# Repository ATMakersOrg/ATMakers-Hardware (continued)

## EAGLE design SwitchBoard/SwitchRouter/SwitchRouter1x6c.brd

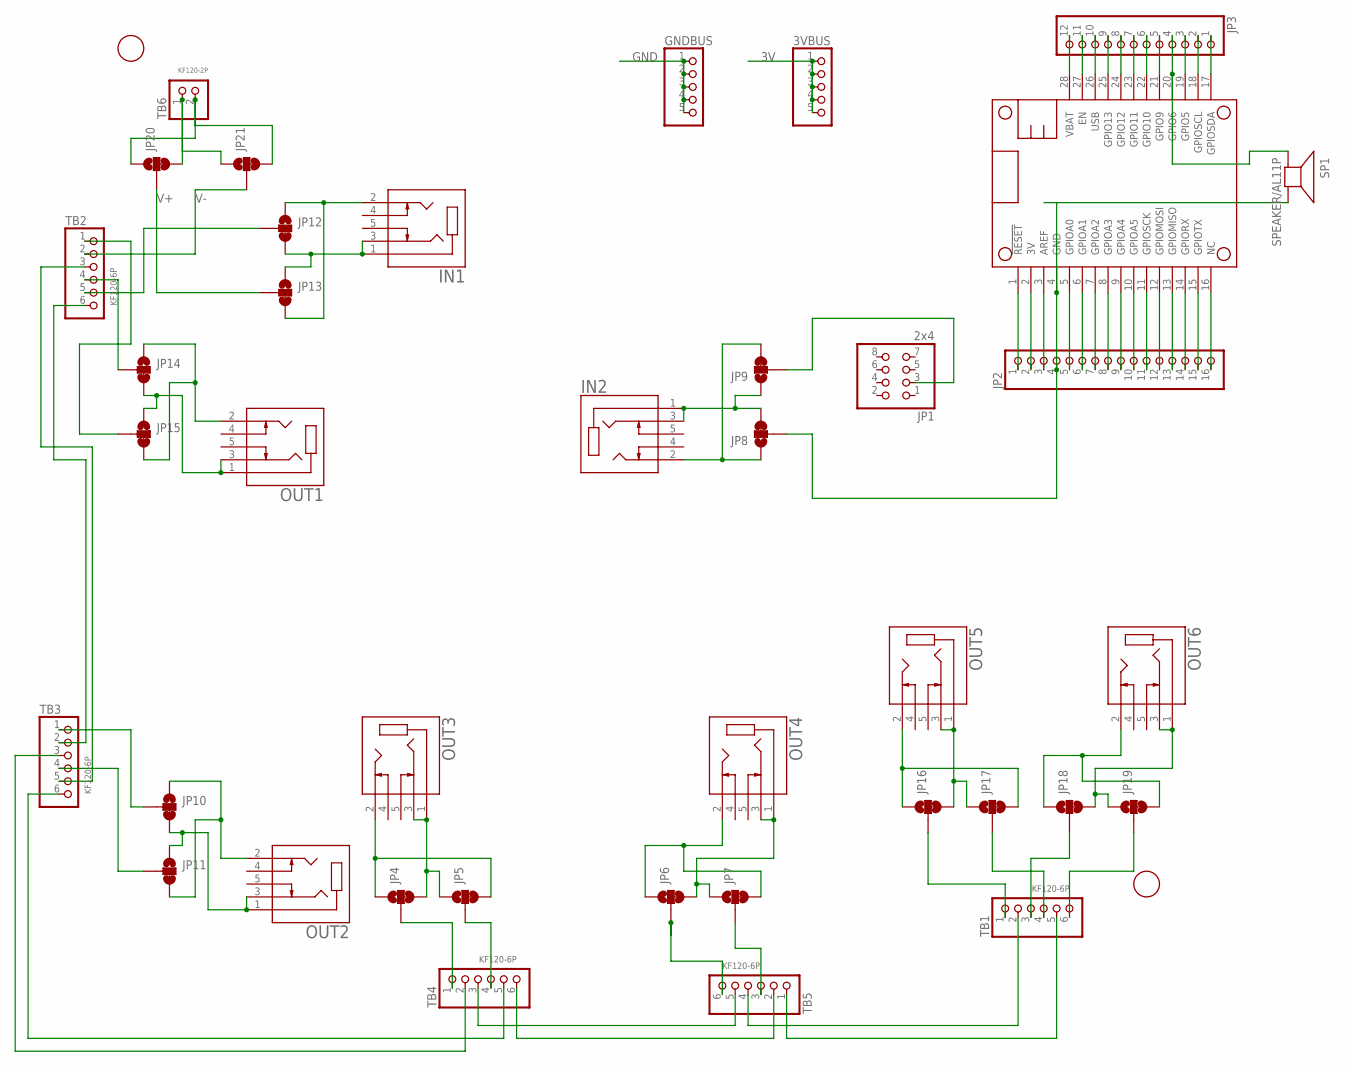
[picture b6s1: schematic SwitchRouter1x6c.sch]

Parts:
3VBUS: PINHD-1X55X2MM; 1_05X2MM
GNDBUS: PINHD-1X55X2MM; 1_05X2MM
IN1, IN2: SJ1-3535NG-PI; CUI_SJ1-3535NG-PI
JP1: 2x4; 2X04
JP2: PINHD-1X16; 1X16
JP3: PINHD-1X12; 1X12
JP4, JP5, JP6, JP7, JP8, JP9, JP10, JP11, JP12, JP13, JP14, JP15, JP16, JP17, JP18, JP19, JP20, JP21: JUMPER-SMT_3_1-NC_TRACE_SILK; SMT-JUMPER_3_1-NC_TRACE_SILK
MS1: FEATHERWING_NODIM; FEATHERWING_DIM
OUT1, OUT2, OUT3, OUT4, OUT5, OUT6: SJ1-3535NG-PI; CUI_SJ1-3535NG-PI
SP1: SPEAKER/AL11P; AL11P
TB1, TB2, TB3, TB4, TB5: KF120-6P; KF120-6P_ROUND
TB6: KF120-2P; KF120-2P_ROUND
U$2, U$3: FIDUCIAL; FIDUCIAL_1MM

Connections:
3V: 3VBUS.1, 3VBUS.2, 3VBUS.3, 3VBUS.4, 3VBUS.5, JP2.2, MS1.2 (3V)
GND: GNDBUS.1, GNDBUS.2, GNDBUS.3, GNDBUS.4, GNDBUS.5, JP2.4, JP8.2, MS1.4 (GND), SP1.-
unnamed: JP2.3, MS1.3 (AREF)
unnamed: JP11.2, TB3.4
unnamed: JP2.5, MS1.5 (GPIOA0)
unnamed: JP2.6, MS1.6 (GPIOA1)
unnamed: JP2.7, MS1.7 (GPIOA2)
unnamed: JP2.8, MS1.8 (GPIOA3)
unnamed: JP2.9, MS1.9 (GPIOA4)
unnamed: JP2.10, MS1.10 (GPIOA5)
unnamed: JP2.11, MS1.11 (GPIOSCK)
unnamed: JP2.12, MS1.12 (GPIOMOSI)
unnamed: JP2.13, MS1.13 (GPIOMISO)
unnamed: JP2.14, MS1.14 (GPIORX)
unnamed: JP2.15, MS1.15 (GPIOTX)
unnamed: JP2.16, MS1.16 (NC)
unnamed: JP3.3, MS1.19 (GPIO5)
unnamed: JP4.1, JP5.3, OUT3.2
unnamed: JP4.3, JP5.1, OUT3.1, OUT3.3
unnamed: JP2.1, MS1.1 (!RESET)
unnamed: JP3.4, MS1.20 (GPIO6), SP1.+
unnamed: JP3.5, MS1.21 (GPIO9)
unnamed: JP3.6, MS1.22 (GPIO10)
unnamed: JP3.7, MS1.23 (GPIO11)
unnamed: JP3.8, MS1.24 (GPIO12)
unnamed: JP4.2, TB4.1
unnamed: JP6.1, JP7.3, OUT4.2
unnamed: JP6.3, JP7.1, OUT4.1, OUT4.3
unnamed: JP5.2, TB4.4
unnamed: JP6.2, TB5.6
unnamed: JP7.2, TB5.3
unnamed: IN2.2, JP8.1, JP9.3
unnamed: IN2.1, IN2.3, JP8.3, JP9.1
unnamed: TB3.6, TB4.5
unnamed: TB1.2, TB5.4
unnamed: JP10.2, TB3.1
unnamed: TB3.3, TB4.2
unnamed: JP10.1, JP11.3, OUT2.2
unnamed: JP10.3, JP11.1, OUT2.1, OUT2.3
unnamed: IN1.2, JP12.1, JP13.3
unnamed: IN1.1, IN1.3, JP12.3, JP13.1
unnamed: TB1.5, TB5.1
unnamed: JP20.3, JP21.1, TB6.1
unnamed: JP20.1, JP21.3, TB6.2
unnamed: JP15.2, TB2.1
unnamed: JP3.1, MS1.17 (GPIOSDA)
unnamed: JP14.1, JP15.3, OUT1.2
unnamed: JP14.3, JP15.1, OUT1.1, OUT1.3
unnamed: JP14.2, TB2.4
unnamed: TB2.3, TB3.5
unnamed: TB2.6, TB3.2
unnamed: JP16.1, JP17.3, OUT5.2
unnamed: JP3.9, MS1.25 (GPIO13)
unnamed: JP16.3, JP17.1, OUT5.1, OUT5.3
unnamed: JP18.1, JP19.3, OUT6.2
unnamed: JP18.3, JP19.1, OUT6.1, OUT6.3
unnamed: JP17.2, TB1.4
unnamed: TB4.3, TB5.5
unnamed: JP19.2, TB1.6
unnamed: JP1.3, JP9.2
unnamed: TB4.6, TB5.2
unnamed: JP16.2, TB1.1
unnamed: JP3.11, MS1.27 (EN)
unnamed: JP12.2, TB2.5
unnamed: JP18.2, TB1.3
SCL: JP3.2, MS1.18 (GPIOSCL)
USB: JP3.10, MS1.26 (USB)
V+: JP13.2, JP20.2
V-: JP21.2, TB2.2
VBAT: JP3.12, MS1.28 (VBAT)

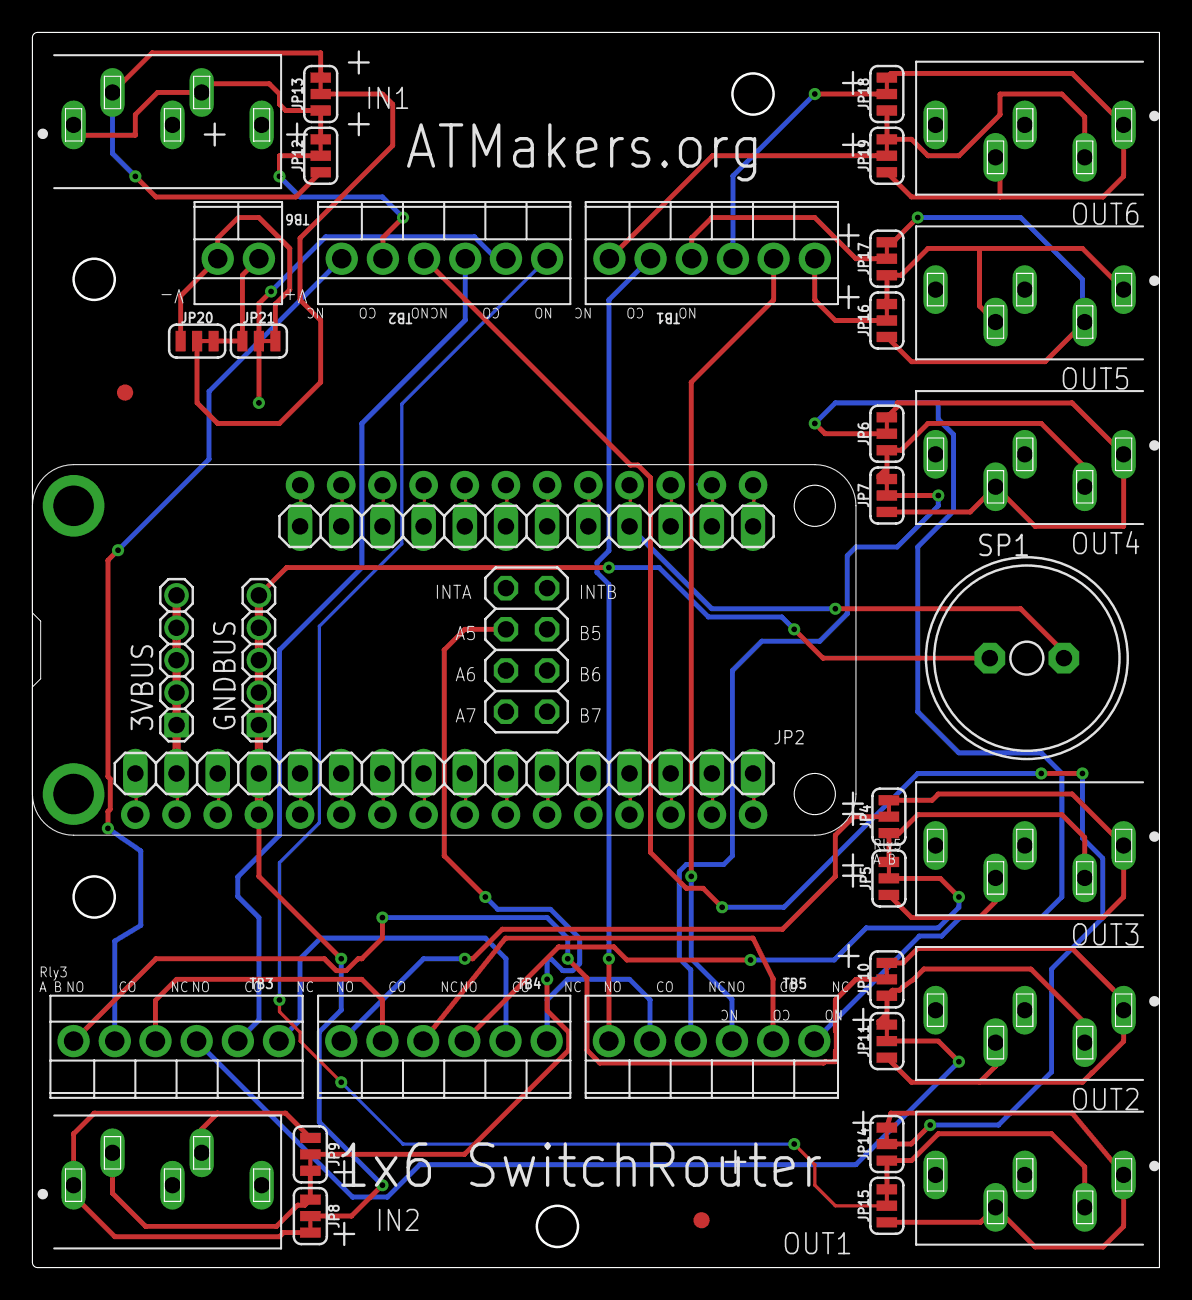
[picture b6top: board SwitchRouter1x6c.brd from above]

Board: 2 copper layers, 69.5 x 76.2 mm, 41 parts (0 on the bottom side), 70 nets.

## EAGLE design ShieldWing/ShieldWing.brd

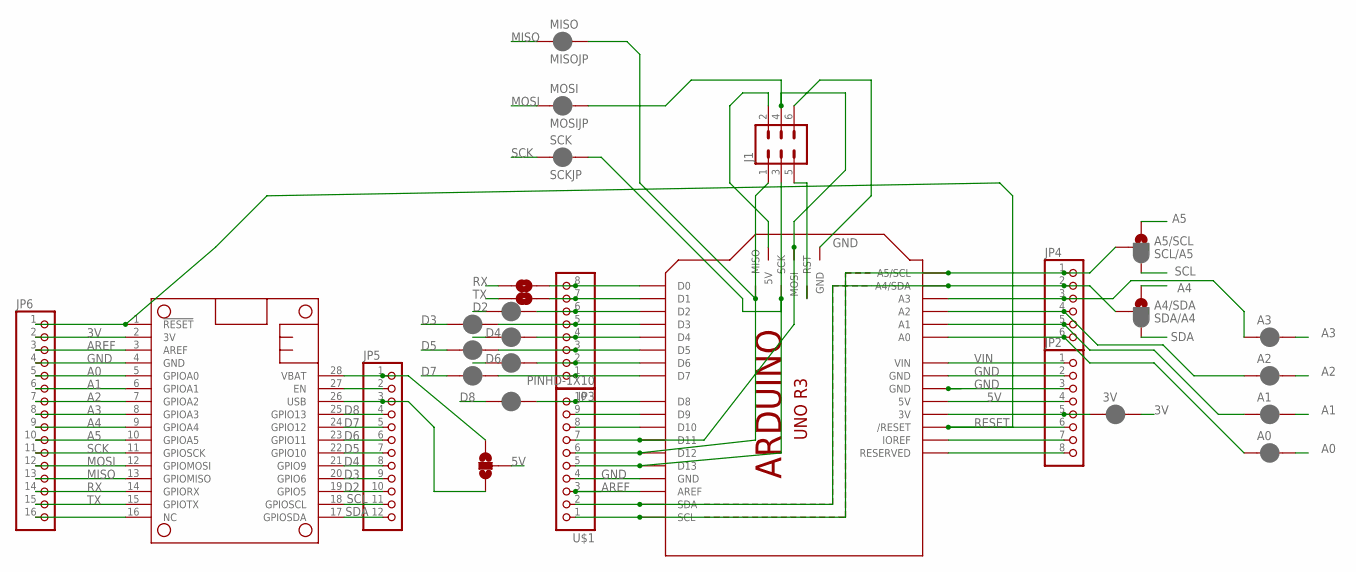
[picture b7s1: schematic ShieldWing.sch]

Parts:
3V: JUMPER-SMT_2_NC_PASTE_SILK; SMT-JUMPER_2_NC_PASTE_SILK
5V: JUMPER-SMT_3_NO_SILK; SMT-JUMPER_3_NO_SILK
A0, A1, A2, A3: JUMPER-SMT_2_NC_PASTE_SILK; SMT-JUMPER_2_NC_PASTE_SILK
A4/SDA: SDA/A4; SMT-JUMPER_3_1-NC_PASTE_SILK
A5/SCL: SCL/A5; SMT-JUMPER_3_1-NC_PASTE_SILK
D2, D3, D4, D5, D6, D7, D8: JUMPER-SMT_2_NC_PASTE_SILK; SMT-JUMPER_2_NC_PASTE_SILK
J1: CONN_03X22X3_SILK_MALE_PTH; 2X3
JP2, JP3: PINHD-1X8CLEANBIG; 1X08-CLEANBIG
JP4: PINHD-1X6B; 1X06-BIG
JP5: PINHD-1X12; 1X12
JP6: PINHD-1X16; 1X16
M1: ARDUINO_R3_ICSP_NODIM; ARDUINOR3_ICSP_NODIM
MISO: MISOJP; SMT-JUMPER_2_NC_PASTE_SILK
MOSI: MOSIJP; SMT-JUMPER_2_NC_PASTE_SILK
MS1: FEATHERWING_NODIM; FEATHERWING_DIM
RX: JUMPER-SMT_2_NO_SILK; SMT-JUMPER_2_NO_SILK
SCK: SCKJP; SMT-JUMPER_2_NC_PASTE_SILK
TX: JUMPER-SMT_2_NO_SILK; SMT-JUMPER_2_NO_SILK
U$1: PINHD-1X10; 1X10-BIG

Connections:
3V: 3V.2, JP6.2, MS1.2 (3V)
5V: 5V.2, JP2.4, M1.5V
A0: A0.2, JP6.5, MS1.5 (GPIOA0)
A1: A1.2, JP6.6, MS1.6 (GPIOA1)
A2: A2.2, JP6.7, MS1.7 (GPIOA2)
A3: A3.2, JP6.8, MS1.8 (GPIOA3)
A4: A4/SDA.1, JP6.9, MS1.9 (GPIOA4)
A5: A5/SCL.1, JP6.10, MS1.10 (GPIOA5)
AREF: JP6.3, M1.AREF, MS1.3 (AREF), U$1.3
D2: D2.1, JP5.10, MS1.19 (GPIO5)
D3: D3.1, JP5.9, MS1.20 (GPIO6)
D4: D4.1, JP5.8, MS1.21 (GPIO9)
D5: D5.1, JP5.7, MS1.22 (GPIO10)
D6: D6.1, JP5.6, MS1.23 (GPIO11)
D7: D7.1, JP5.5, MS1.24 (GPIO12)
D8: D8.1, JP5.4, MS1.25 (GPIO13)
GND: J1.6, JP2.2, JP2.3, JP6.4, M1.GND, M1.GND@1 (GND), M1.GND@2 (GND), M1.GND@3 (GND), MS1.4 (GND), U$1.4
MISO: JP6.13, MISO.1, MS1.13 (GPIOMISO)
MOSI: JP6.12, MOSI.1, MS1.12 (GPIOMOSI)
unnamed: JP3.7, M1.D1, TX.2
unnamed: JP3.8, M1.D0, RX.2
unnamed: JP5.2, MS1.27 (EN)
unnamed: A4/SDA.2, JP4.2, M1.A4 (A4/SDA), M1.SDA, U$1.2
unnamed: A5/SCL.2, JP4.1, M1.A5 (A5/SCL), M1.SCL, U$1.1
unnamed: 3V.1, JP2.5, M1.3V
unnamed: A3.1, JP4.3, M1.A3
unnamed: A2.1, JP4.4, M1.A2
unnamed: A1.1, JP4.5, M1.A1
unnamed: A0.1, JP4.6, M1.A0
unnamed: JP2.7, M1.IOREF
unnamed: JP2.8, M1.RESERVED
unnamed: J1.3, M1.D13, M1.SCK, SCK.2, U$1.5
unnamed: J1.1, M1.D12, M1.MISO, MISO.2, U$1.6
unnamed: J1.4, M1.D11, M1.MOSI, MOSI.2, U$1.7
unnamed: M1.D10, U$1.8
unnamed: M1.D9, U$1.9
unnamed: D8.2, M1.D8, U$1.10
unnamed: D7.2, JP3.1, M1.D7
unnamed: D6.2, JP3.2, M1.D6
unnamed: D5.2, JP3.3, M1.D5
unnamed: D4.2, JP3.4, M1.D4
unnamed: D3.2, JP3.5, M1.D3
unnamed: D2.2, JP3.6, M1.D2
unnamed: J1.2, M1.5V_ICSP (5V)
unnamed: J1.5, M1.RESET_ICSP (RST)
unnamed: JP6.16, MS1.16 (NC)
RESET: JP2.6, JP6.1, M1.RESET (/RESET), MS1.1 (!RESET)
RX: JP6.14, MS1.14 (GPIORX), RX.1
SCK: JP6.11, MS1.11 (GPIOSCK), SCK.1
SCL: A5/SCL.3, JP5.11, MS1.18 (GPIOSCL)
SDA: A4/SDA.3, JP5.12, MS1.17 (GPIOSDA)
TX: JP6.15, MS1.15 (GPIOTX), TX.1
USB: 5V.1, JP5.3, MS1.26 (USB)
VBAT: 5V.3, JP5.1, MS1.28 (VBAT)
VIN: JP2.1, M1.VIN

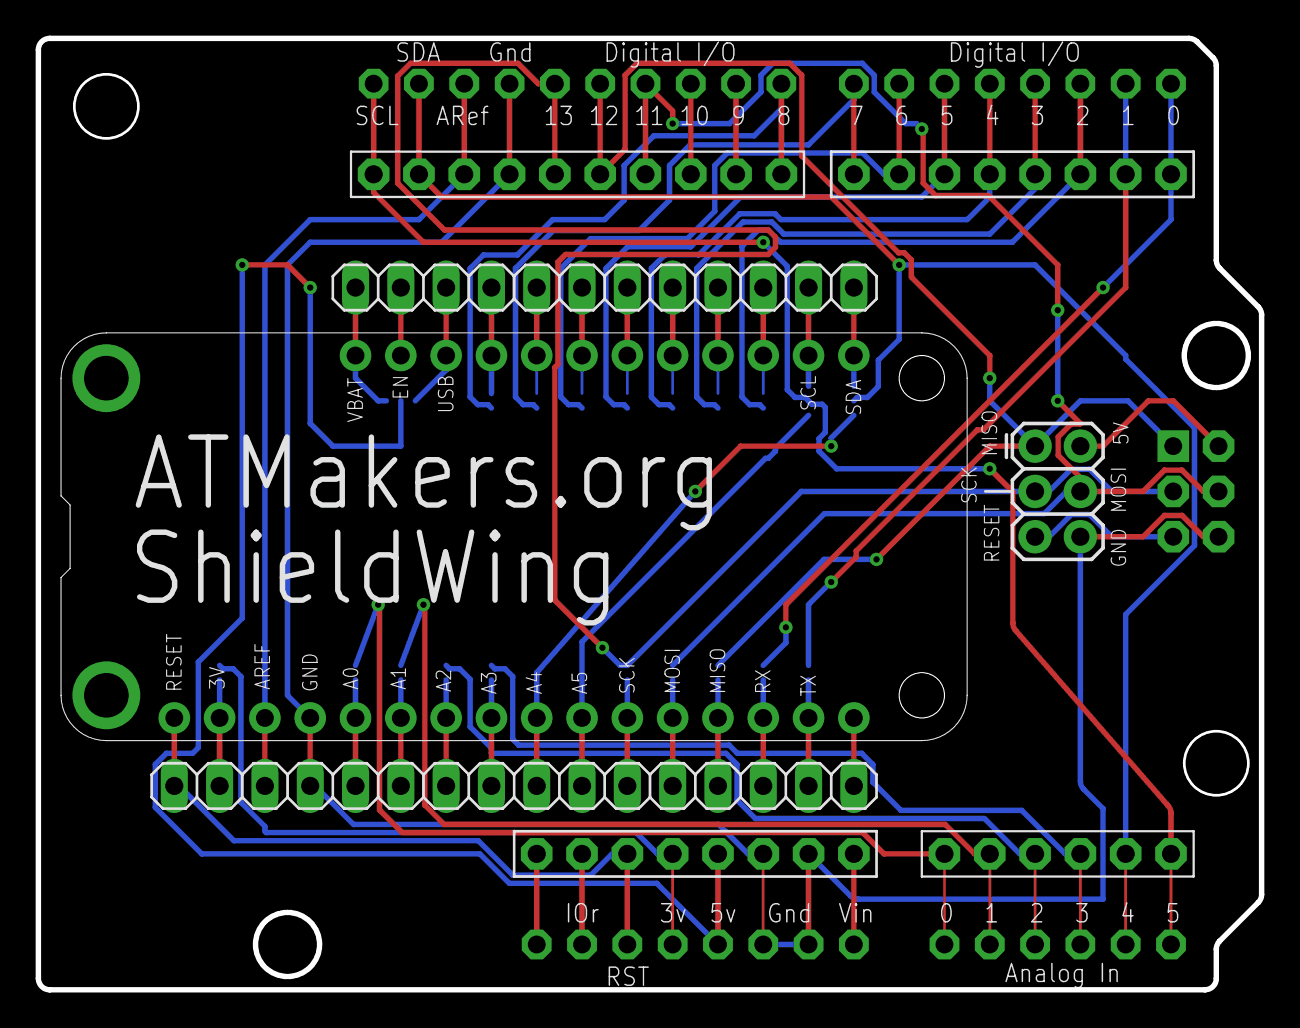
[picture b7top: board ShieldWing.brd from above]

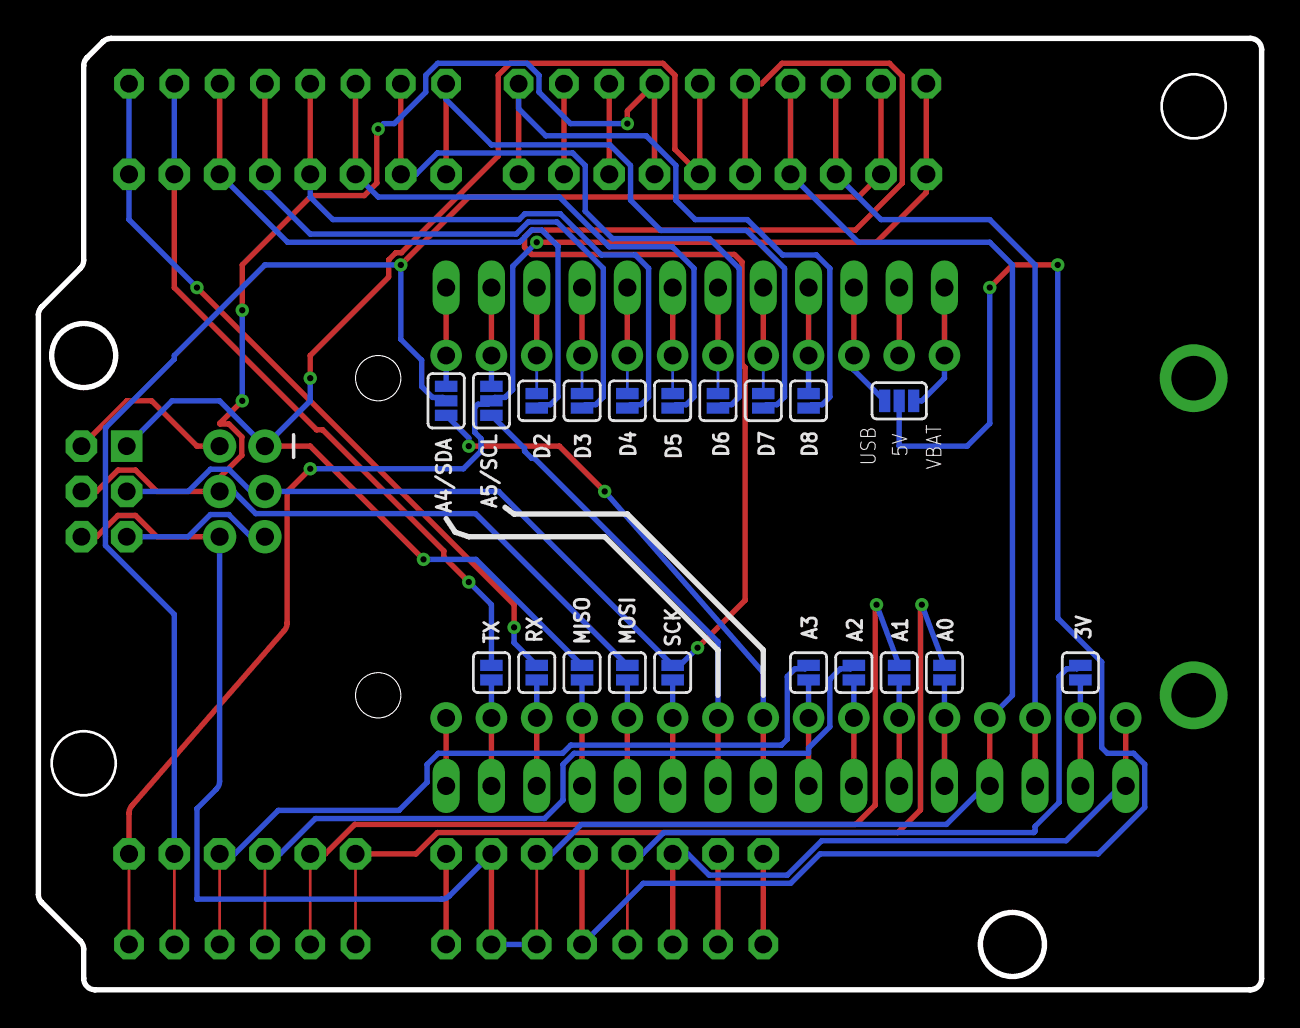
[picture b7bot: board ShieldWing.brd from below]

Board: 2 copper layers, 68.6 x 53.3 mm, 29 parts (20 on the bottom side), 55 nets.

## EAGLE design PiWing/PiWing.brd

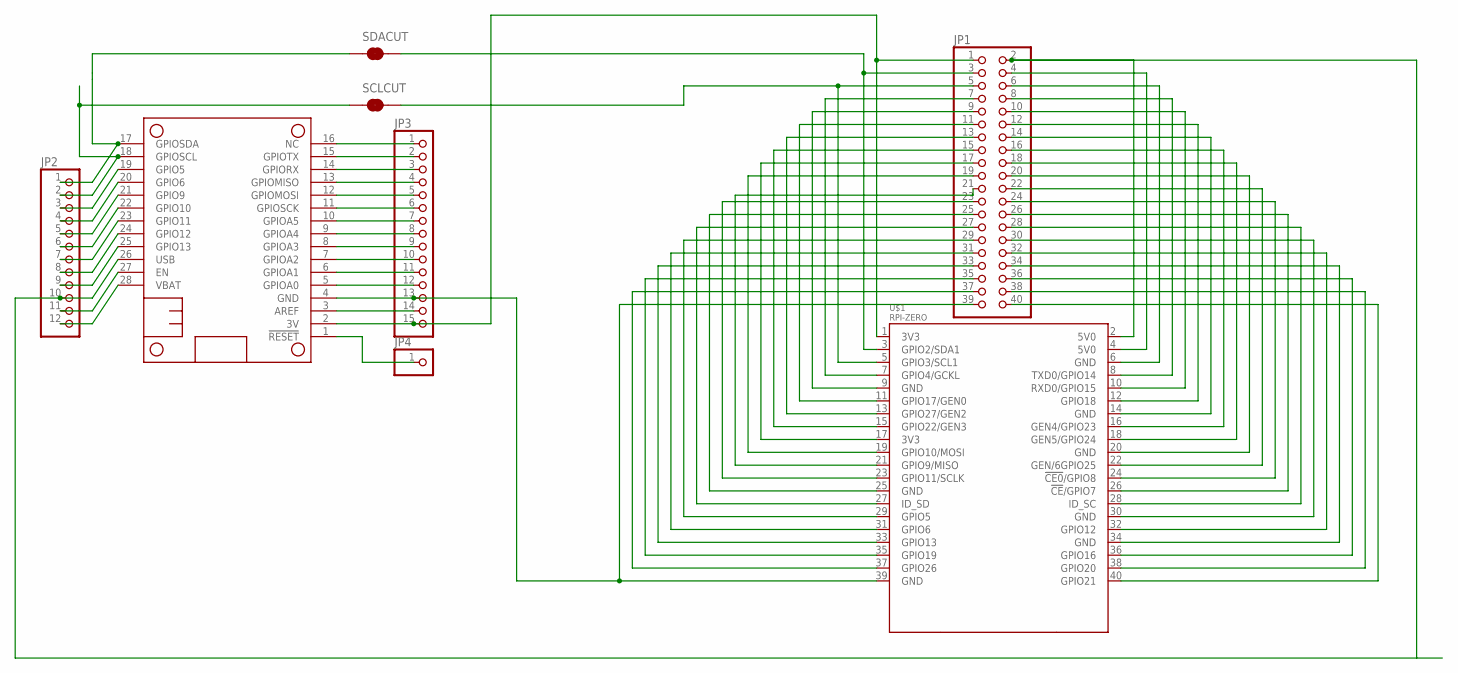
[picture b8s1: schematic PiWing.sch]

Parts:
JP1: PINHD-2X20-BIG; 2X20-BIG
JP2: PINHD-1X12-CB; 1X12-CB
JP3: PINHD-1X15-CB; 1X15-CB
JP4: PINHD-1X1CB; 1X01-CLEANBIG
MS1: FEATHERWING_NODIM; FEATHERWING_DIM
SCLCUT: JUMPER-SMT_2_NC_TRACE_SILK; SMT-JUMPER_2_NC_TRACE_SILK
SDACUT: JUMPER-SMT_2_NC_TRACE_SILK; SMT-JUMPER_2_NC_TRACE_SILK
U$1: RPI-ZERO; RASPBERRYPI_BASTELSTUBE_V13_RASPI_BOARD_B+_FULL

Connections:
3V: JP1.1, JP3.15, MS1.2 (3V), U$1.1 (3V3)
3V3@2: JP1.17, U$1.17 (3V3)
5V0@2: JP1.4, U$1.4 (5V0)
GND@1: JP1.9, U$1.9 (GND)
GND@2: JP1.25, U$1.25 (GND)
GND@3: JP1.39, JP3.13, MS1.4 (GND), U$1.39 (GND)
GND@4: JP1.14, U$1.14 (GND)
GND@5: JP1.20, U$1.20 (GND)
GND@6: JP1.30, U$1.30 (GND)
GND@7: JP1.34, U$1.34 (GND)
GND@8: JP1.6, U$1.6 (GND)
unnamed: JP1.3, SDACUT.2, U$1.3 (GPIO2/SDA1)
unnamed: JP1.5, SCLCUT.2, U$1.5 (GPIO3/SCL1)
unnamed: JP2.3, MS1.19 (GPIO5)
unnamed: JP2.4, MS1.20 (GPIO6)
unnamed: JP2.5, MS1.21 (GPIO9)
unnamed: JP2.6, MS1.22 (GPIO10)
unnamed: JP2.7, MS1.23 (GPIO11)
unnamed: JP2.8, MS1.24 (GPIO12)
unnamed: JP2.9, MS1.25 (GPIO13)
unnamed: JP2.11, MS1.27 (EN)
unnamed: JP3.1, MS1.16 (NC)
unnamed: JP3.2, MS1.15 (GPIOTX)
unnamed: JP3.3, MS1.14 (GPIORX)
unnamed: JP1.21, U$1.21 (GPIO9/MISO)
unnamed: JP1.19, U$1.19 (GPIO10/MOSI)
unnamed: JP1.23, U$1.23 (GPIO11/SCLK)
unnamed: JP3.7, MS1.10 (GPIOA5)
unnamed: JP3.8, MS1.9 (GPIOA4)
unnamed: JP3.9, MS1.8 (GPIOA3)
unnamed: JP3.10, MS1.7 (GPIOA2)
unnamed: JP3.11, MS1.6 (GPIOA1)
unnamed: JP3.12, MS1.5 (GPIOA0)
unnamed: JP3.6, MS1.11 (GPIOSCK)
unnamed: JP3.14, MS1.3 (AREF)
unnamed: JP4.1, MS1.1 (!RESET)
unnamed: JP1.11, U$1.11 (GPIO17/GEN0)
unnamed: JP3.5, MS1.12 (GPIOMOSI)
unnamed: JP3.4, MS1.13 (GPIOMISO)
unnamed: JP1.7, U$1.7 (GPIO4/GCKL)
unnamed: JP1.13, U$1.13 (GPIO27/GEN2)
unnamed: JP1.15, U$1.15 (GPIO22/GEN3)
unnamed: JP1.27, U$1.27 (ID_SD)
unnamed: JP2.1, MS1.17 (GPIOSDA), SDACUT.1
unnamed: JP2.2, MS1.18 (GPIOSCL), SCLCUT.1
unnamed: JP1.29, U$1.29 (GPIO5)
unnamed: JP1.31, U$1.31 (GPIO6)
unnamed: JP1.33, U$1.33 (GPIO13)
unnamed: JP1.35, U$1.35 (GPIO19)
unnamed: JP1.37, U$1.37 (GPIO26)
unnamed: JP1.16, U$1.16 (GEN4/GPIO23)
unnamed: JP1.18, U$1.18 (GEN5/GPIO24)
unnamed: JP1.8, U$1.8 (TXD0/GPIO14)
unnamed: JP1.10, U$1.10 (RXD0/GPIO15)
unnamed: JP1.12, U$1.12 (GPIO18)
unnamed: JP1.22, U$1.22 (GEN/6GPIO25)
unnamed: JP1.24, U$1.24 (!CE0!/GPIO8)
unnamed: JP1.26, U$1.26 (!CE!/GPIO7)
unnamed: JP1.28, U$1.28 (ID_SC)
unnamed: JP1.32, U$1.32 (GPIO12)
unnamed: JP1.36, U$1.36 (GPIO16)
unnamed: JP1.38, U$1.38 (GPIO20)
unnamed: JP1.40, U$1.40 (GPIO21)
USB: JP1.2, JP2.10, MS1.26 (USB), U$1.2 (5V0)
VBAT: JP2.12, MS1.28 (VBAT)

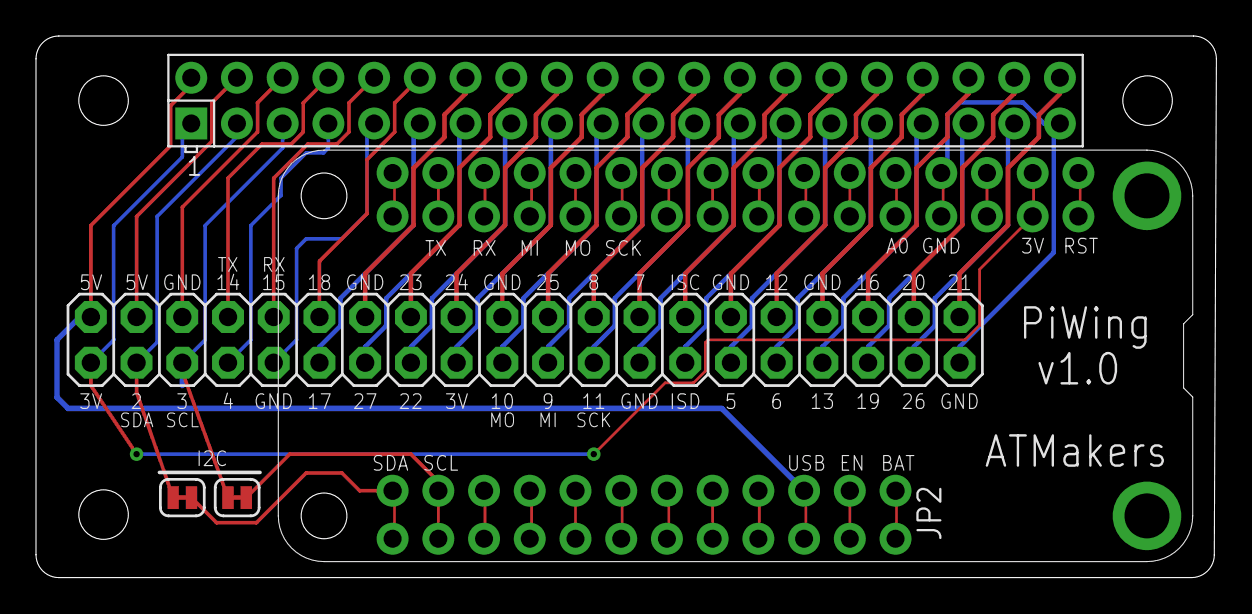
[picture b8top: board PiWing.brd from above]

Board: 2 copper layers, 65.6 x 30.1 mm, 8 parts (0 on the bottom side), 65 nets.

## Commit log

2018-03-10 Fix contact labels.
    Moved relays, labeled between pads. Cleaned up schematic around R1. Reviewed schematic and board. Design rules pass except around left mounting holes.
2018-03-11 Fix Ax pads, rear text.
    Added bRestrict & vRestrict to address pads to keep vias & traces out of cut area. Added new shorted jumper device to prevent routing to GND via Ax. If problems, route w/ SJW then replace w/ SJW-SHOR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
    Added bottom text.
2018-03-11 Move text off vias, rm copied dim line.
    vRestrict ares for labels were lost. Re-apply on re-route.
2018-05-15 Adding first try at silkscreen
    Adding first try at silkscreen
2018-05-16 Increased trace width
2018-05-16 Added wide traces to current sensor
2018-05-16 Ignores temp files
2018-05-17 Fixed RN & GPIO A/B
    New CTS746X101 device (pkg & schem).
    GPIO port A=Set lines + GPIO A5-7
    GPIO port B=Reset lines + GPIO B5-7
2018-05-18 Radius, labels, ERC
    Corners radiused.
    Relay labels added (ex Rly4).
    Fixed one EDC warning.
2018-05-26 No Air Wires
    I worked out the air wires. It's not pretty but it passes the DRC (except for the overlaps around the cut traces.
2018-05-28 Adding Tester
2018-05-30 Updated p/n for relay driver
2018-06-08 tinker with 5pin header
    relay drivers on brd need to be checked, RN1 moved. Ground plated mounting hole(s).
2018-06-08 Added pcbway sheet
2018-06-12 Added 2x2 header & silkscreen changes
    This is a version that has no airwires and has a 2x2 header with the I2C bus and power and ground pulled out. It does NOT have John's part number changes that took place after 5/28
2018-06-12 Adding additional Silkscreen tweaks
2018-06-13 sch: RN GPIO radius fixes brd: no airwires
    This reverts to my May 17 sch file which fixed the resistor network part and GPIO signals followed by Bill's May 26 routed brd file.
2018-06-13 Adding Pi Wing
2018-06-13 Added 4-pin 12c header (no silkscreen changes yet)
2018-06-13 Added Silkscreen changes
2018-06-13 Added updated PiWing
2018-06-13 Small tweak to generate tented vias
2018-06-13 Updated PiWing
2018-06-13 Flipped edge text and sending to PCBWay
2018-07-03 Adding ShieldWing
    Adding ShieldWing
2018-07-03 Removing crap
2018-07-03 Removing Zip File
2018-08-14 Adding some boards
2018-09-16 Rev B (start)
    First commit for Rev B. See updated Description.
2018-09-20 Users Guide (started)
    Users Guide outline and some content.
2018-09-20 more content
    Added Library details and board revision info. Removed document version in favor of date.
2018-09-21 more routing
    More routing and clean DRC items. Some airwires remain.
2018-09-21 resistor & routing changes
    Added LED resistor, resized resisitor to 0603, relocate reset cap.
2018-09-22 board 100% routed
    DRC clean with some very minor exceptions.
2018-09-22 "POWER" text, manual
    Moved text, documented headers.
2019-02-24 Rev B Silkscreen
    Added silkscreen to back & prepped for board manufacturing. Make sure to set mask limit to 45 mils to get the tented vias correct on this board. For some reason that's not captured in the .BRD file.
2019-02-26 Flipped text outward on upper edge.
    Rotated and spun text on upper edge to face outward.
2019-03-18 Adding Rev B changes for the Tester
2019-03-19 Updating tester
2019-03-19 Restoring good BRD file to match that built.
2019-03-19 Moved resistor to the ground-side of the current sensor
2019-03-19 Latest update after sending to PCBWay
2019-07-12 Adding KeySwitch
    Adding KeySwitch
2019-07-12 Create KeySwitchGerbers.zip
    Adding Gerbers
2019-08-10 Adding Joystick Board
2019-08-10 Adding Picture
2019-08-11 Added NeoPixel w/jumper & pin
2019-08-11 Updated to add neopixel & jumper - no air wires
2019-08-11 Added User Switch Output
2019-08-11 Removed transistor
2019-08-11 No AirWires & ready for reset button and double check
2019-08-11 Update with address pads
2019-08-12 Added the missing Neopixel led pads and updated the switch to DTS-3: 3.5x6mm style switch.
2019-08-12 Revert "Added the missing Neopixel led pads and updated the switch to DTS-3: 3.5x6mm style switch."
    This reverts commit 7139ee0b9ca13871835c94f32c5504dad1631a27.
2019-08-12 Added milad.lib and removed backup files.
2019-08-12 Cleaning up for manu
    Added restriction around traces for the jumpers
    Added text and a place for the PCBWay product num
    Replaced pins to be consistent
2019-08-12 Update JoystickWing.brd
    Adding boxes around the breakouts
2019-08-12 Added .gitignore
    Adding .gitignore
2019-08-13 Added BOM file.
2019-08-13 Updated BOM File.
2019-08-13 Added Ext Price and Total
2019-08-15 Updated to fix errors and sent to PCBWay
2019-08-15 Removed Adafruit Logos
2021-02-22 Removed bad V+ connection and cleaned up
2022-09-07 Adding TwiddleStick Board
